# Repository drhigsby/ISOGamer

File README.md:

# ISOGamer
 ISOGamer is a uniform staggered van-like keyboard that supports 2x ISO keys and a left-sided rotary encoder.

Required Hardware for stacked case design:

-4x binding barrels https://www.mcmaster.com/93121A337/

-14x m2 5mm flat head screws https://www.aliexpress.com/item/4000067543700.html

-4x m2 5mm round standoffs  https://www.aliexpress.com/item/4000022968613.html

-6x m2 8mm flat head screws https://www.aliexpress.com/item/4000067543700.html

-6x m2 8mm round standoffs https://www.aliexpress.com/item/4000022968613.html

-1.5mm rubber bumpons (for mounting the plate)

-diodes(smd or tht)

-PM or equivalent

-rotary encoder (optional)

-switches

-keycaps

-2x3u stabilizers (for 2x3u bar option) OR 1x6.25u stabilizer (for 6.25u bar option)

KLE: http://www.keyboard-layout-editor.com/#/gists/59bec7c24a2eacc7034534ae54d9d0a9

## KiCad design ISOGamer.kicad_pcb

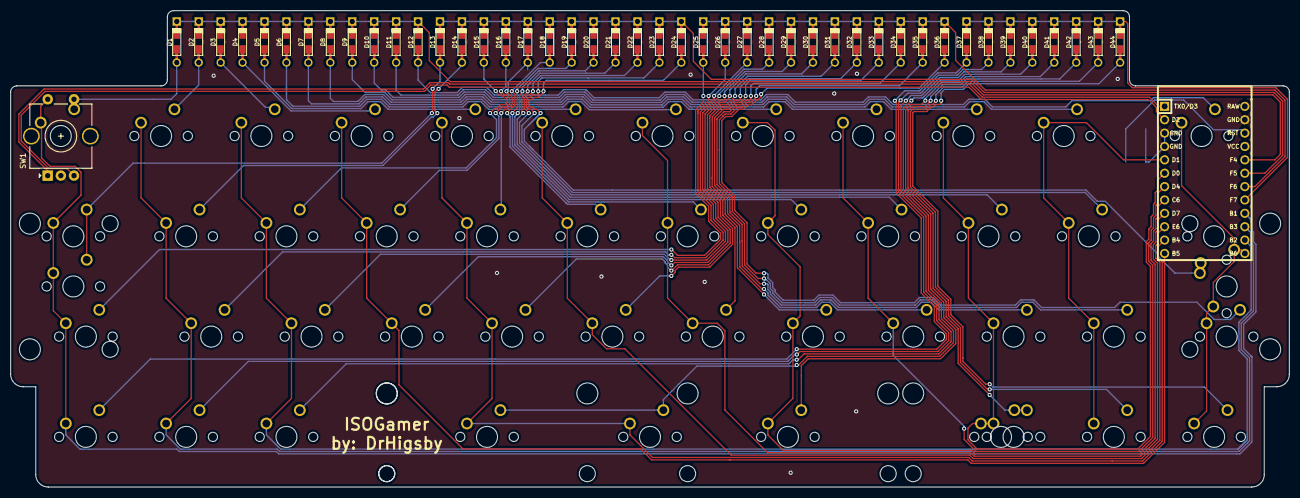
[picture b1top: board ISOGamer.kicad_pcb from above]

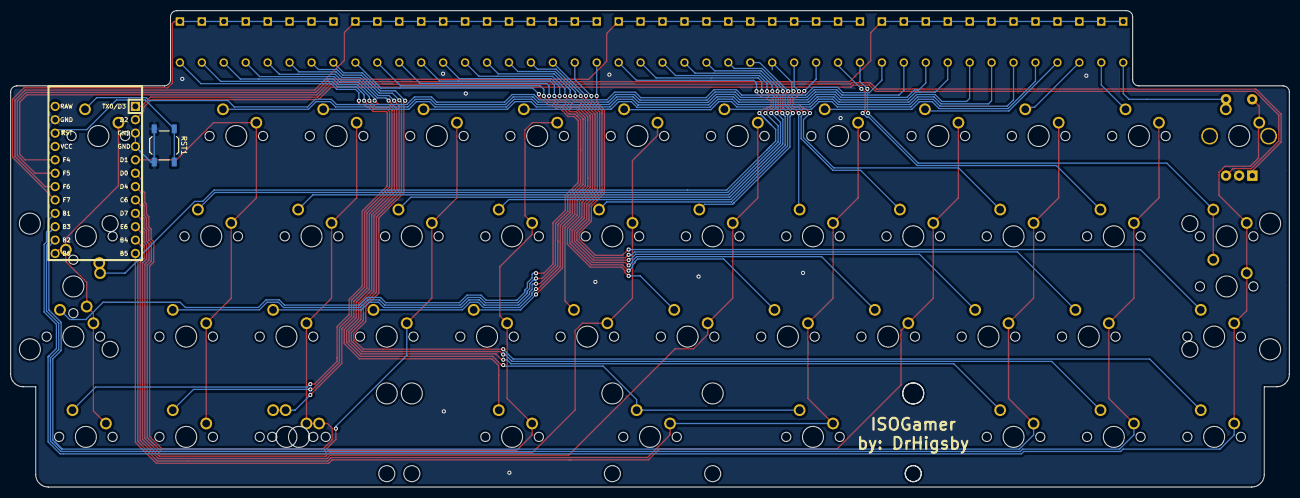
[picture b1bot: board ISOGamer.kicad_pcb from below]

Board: 2 copper layers, 242.9 x 90.5 mm, 95 parts (45 on the bottom side), 64 nets.

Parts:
D1, D2, D3, D4, D5, D6, D7, D8, D9, D10, D11, D12, D13, D14, D15, D16, D17, D18, D19, D20, D21, D22, D23, D24, D25, D26, D27, D28, D29, D30, D31, D32, D33, D34, D35, D36, D37, D38, D39, D40, D41, D42, D43, D44: D_Small; Diode-Hybrid-Back
MX1, MX2, MX3, MX4, MX5, MX6, MX7, MX8, MX9, MX10, MX11, MX14, MX15, MX16, MX17, MX18, MX19, MX20, MX21, MX22, MX23, MX26, MX27, MX28, MX29, MX30, MX31, MX32, MX33, MX34, MX35, MX37, MX38, MX39, MX42-1, MX43, MX44: MX-NoLED; MXOnly-1U-NoLED
MX12: MX-NoLED; MXOnly-1.75U-NoLED
MX13, MX36, MX42: MX-NoLED; MXOnly-1.25U-NoLED
MX13-ISO1, MX24-ISO1: MX-NoLED; MXOnly-ISO-ROTATED
MX24, MX25: MX-NoLED; MXOnly-1.5U-NoLED
MX40, MX41: MX-NoLED; MXOnly-3U-ReversedStabilizers-NoLED
MX40-6251: MX-NoLED; MXOnly-6.25U-ReversedStabilizers-NoLED
RST1: SW_Push; SW_SPST_TL3342
SW1: Rotary_Encoder_Switch; RotaryEncoder_Alps_EC11E-Switch_Vertical_H20mm_CircularMoun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
U1: ProMicro; ArduinoProMicro

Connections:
C1: MX1.1, MX13.1, MX13-ISO1.1, MX25.1, MX37.1, SW1.S2, U1.16
C2: MX2.1, MX14.1, MX26.1, MX38.1, U1.15
C3: MX3.1, MX15.1, MX27.1, MX39.1, U1.14
C4: MX4.1, MX16.1, MX28.1, U1.12
C5: MX5.1, MX17.1, MX29.1, MX40.1, MX40-6251.1, U1.11
C6: MX6.1, MX18.1, MX30.1, U1.10
C7: MX7.1, MX19.1, MX31.1, U1.9
C8: MX8.1, MX20.1, MX32.1, MX41.1, U1.8
C9: MX9.1, MX21.1, MX33.1, U1.7
C10: MX10.1, MX22.1, MX34.1, MX42.1, MX42-1.1, U1.6
C11: MX11.1, MX23.1, MX35.1, MX43.1, U1.5
C12: MX12.1, MX24.1, MX24-ISO1.1, MX36.1, MX44.1, U1.13
GND: RST1.2, SW1.C, U1.3, U1.4, U1.23
KNOB1: D1.2, MX1.2, SW1.S1
M1: SW1.A, U1.1
M2: SW1.B, U1.2
unnamed: D2.2, MX2.2
unnamed: D3.2, MX3.2
unnamed: D4.2, MX4.2
unnamed: D5.2, MX5.2
unnamed: D6.2, MX6.2
unnamed: D7.2, MX7.2
unnamed: D8.2, MX8.2
unnamed: D9.2, MX9.2
unnamed: D10.2, MX10.2
unnamed: D11.2, MX11.2
unnamed: D12.2, MX12.2
unnamed: D13.2, MX13.2, MX13-ISO1.2
unnamed: D14.2, MX14.2
unnamed: D15.2, MX15.2
unnamed: D16.2, MX16.2
unnamed: D17.2, MX17.2
unnamed: D18.2, MX18.2
unnamed: D19.2, MX19.2
unnamed: D20.2, MX20.2
unnamed: D21.2, MX21.2
unnamed: D22.2, MX22.2
unnamed: D23.2, MX23.2
unnamed: D24.2, MX24.2, MX24-ISO1.2
unnamed: D25.2, MX25.2
unnamed: D26.2, MX26.2
unnamed: D27.2, MX27.2
unnamed: D28.2, MX28.2
unnamed: D29.2, MX29.2
unnamed: D30.2, MX30.2
unnamed: D31.2, MX31.2
unnamed: D32.2, MX32.2
unnamed: D33.2, MX33.2
unnamed: D34.2, MX34.2
unnamed: D35.2, MX35.2
unnamed: D36.2, MX36.2
unnamed: D37.2, MX37.2
unnamed: D38.2, MX38.2
unnamed: D39.2, MX39.2
unnamed: D40.2, MX40.2, MX40-6251.2
unnamed: D41.2, MX41.2
unnamed: D42.2, MX42.2, MX42-1.2
unnamed: D43.2, MX43.2
unnamed: D44.2, MX44.2
R1: D1.1, D2.1, D3.1, D4.1, D5.1, D6.1, D7.1, D8.1, D9.1, D10.1, D11.1, D12.1, U1.20
R2: D13.1, D14.1, D15.1, D16.1, D17.1, D18.1, D19.1, D20.1, D21.1, D22.1, D23.1, D24.1, U1.19
R3: D25.1, D26.1, D27.1, D28.1, D29.1, D30.1, D31.1, D32.1, D33.1, D34.1, D35.1, D36.1, U1.18
R4: D37.1, D38.1, D39.1, D40.1, D41.1, D42.1, D43.1, D44.1, U1.17
RST: RST1.1, U1.22

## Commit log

2021-10-28 readme update
2021-10-28 updating case files
2021-10-28 updating case file names
2021-10-28 qmk update stuff
2021-10-28 fixing compile errors
